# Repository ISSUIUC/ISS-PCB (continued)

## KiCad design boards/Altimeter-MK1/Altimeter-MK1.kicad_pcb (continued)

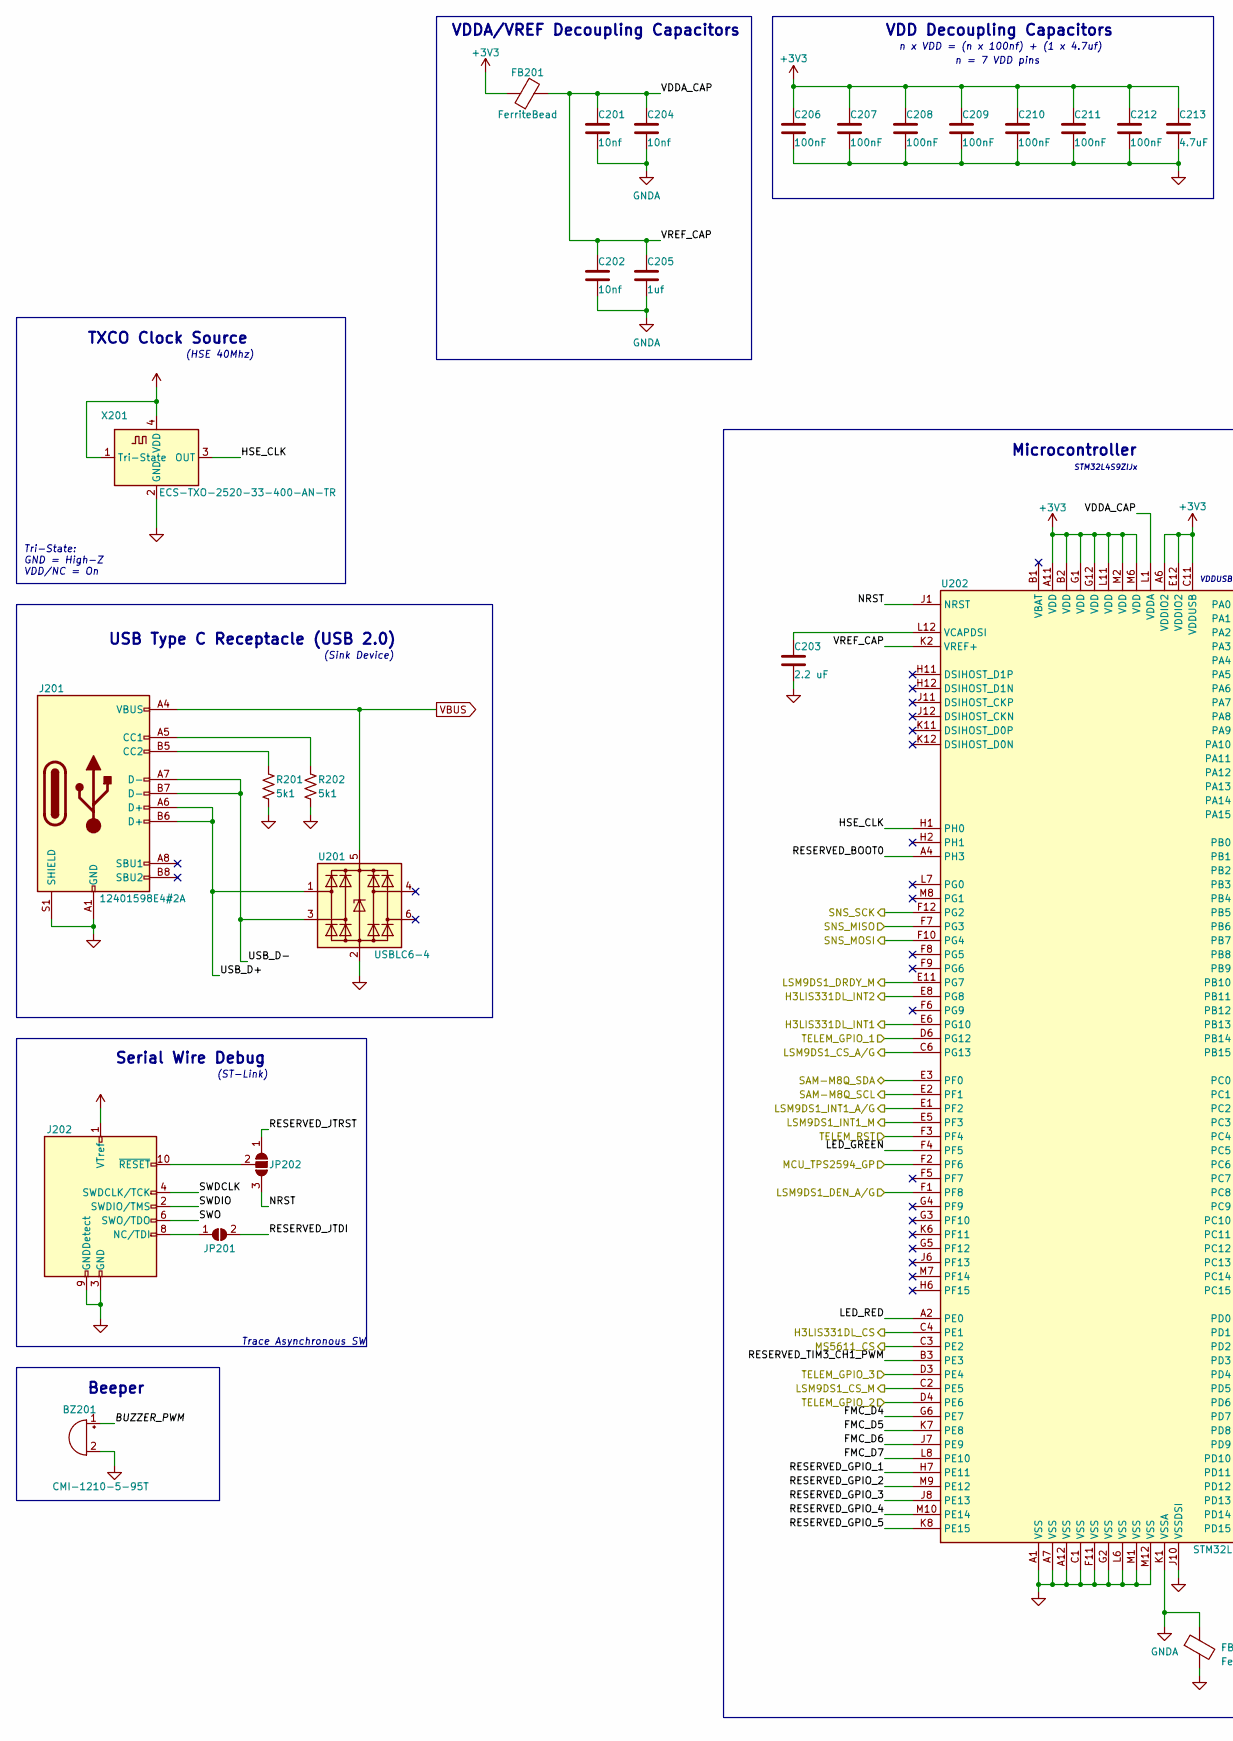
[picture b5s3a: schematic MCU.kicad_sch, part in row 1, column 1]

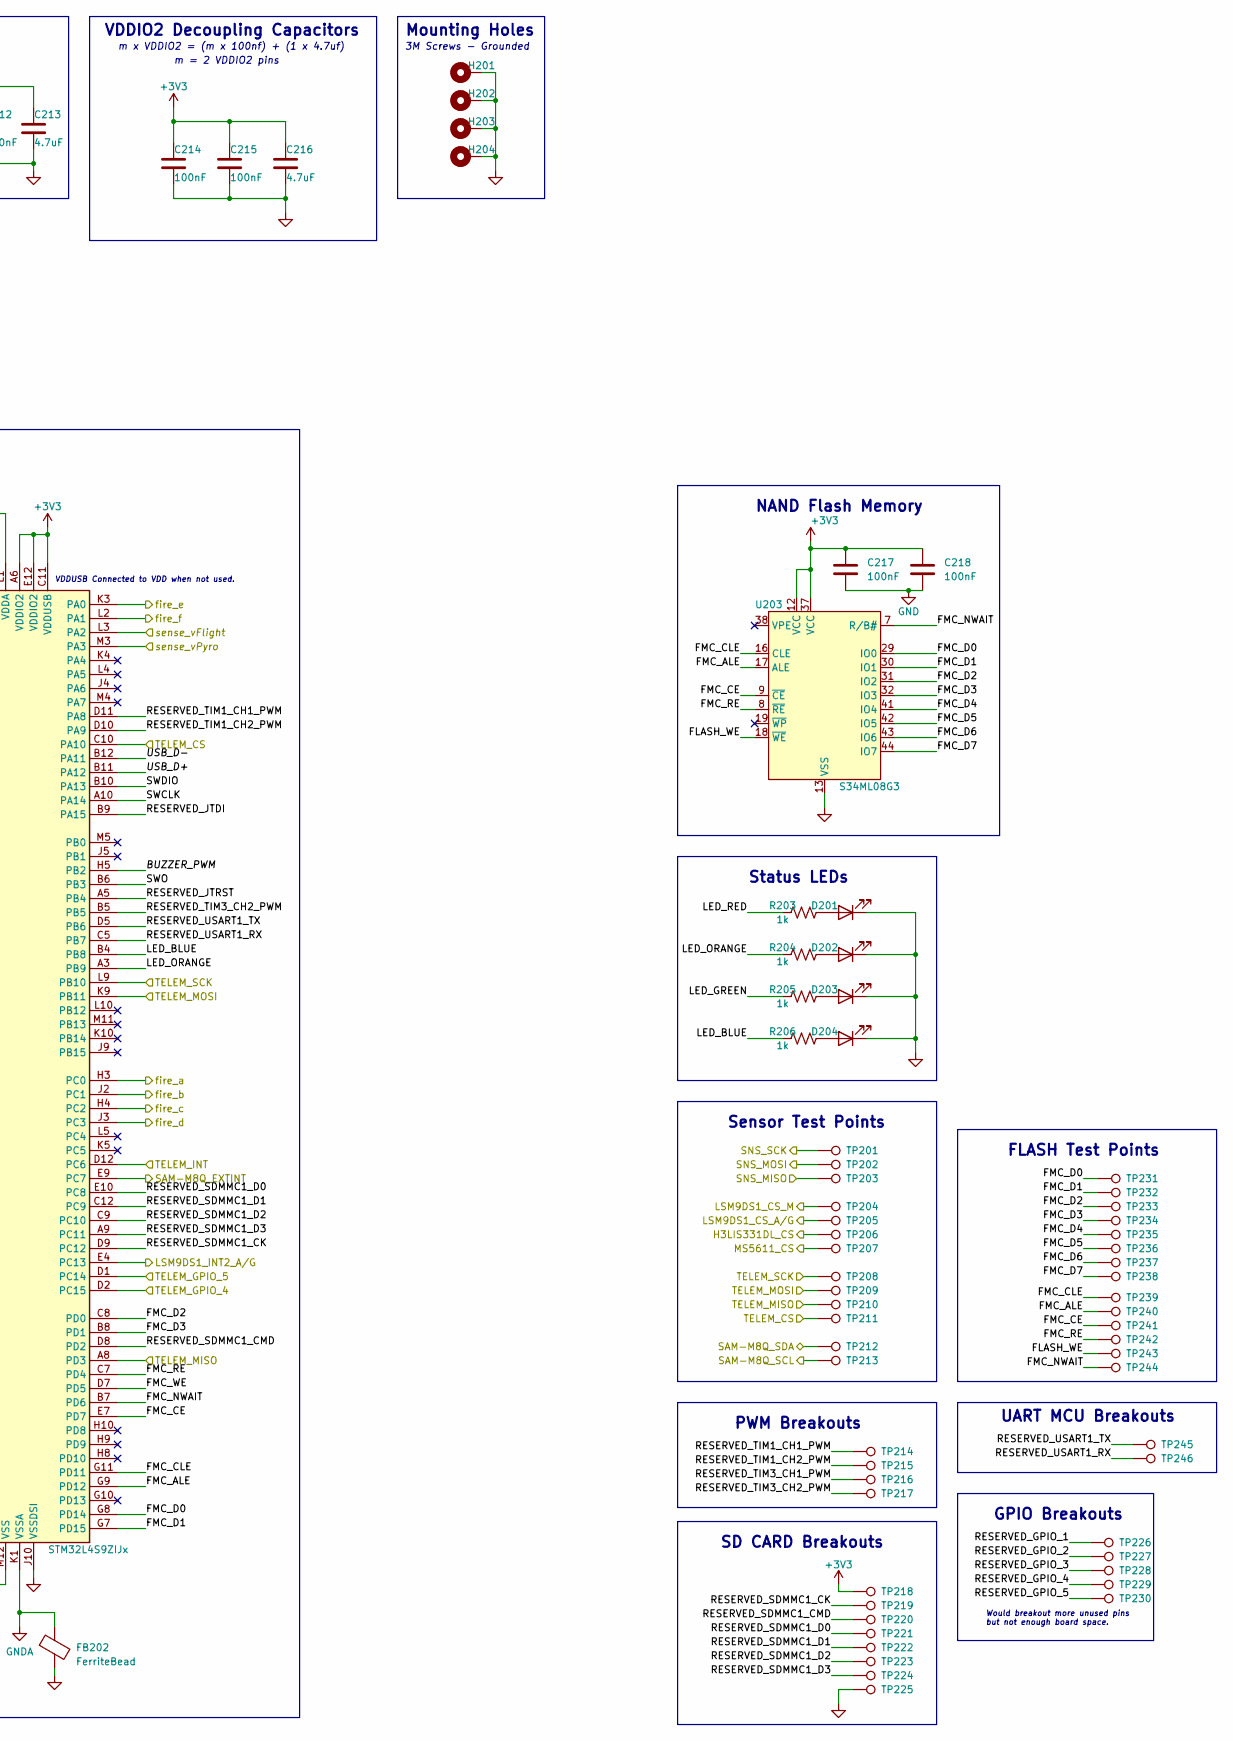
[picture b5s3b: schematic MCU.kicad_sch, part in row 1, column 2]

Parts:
BZ201: CMI-1210-5-95T; MagneticBuzzer_ProSignal_ABI-010-RC
C201, C202, C204: 10nf; C_0603_1608Metric
C203: 2.2 uF; C_0603_1608Metric
C205: 1uf; C_0603_1608Metric
C206, C207, C208, C209, C210, C211, C212, C214, C215, C217, C218: 100nF; C_0603_1608Metric
C213, C216: 4.7uF; C_0603_1608Metric
D201, D202, D203, D204: LED_0603_1608Metric
FB201, FB202: FerriteBead; R_0805_2012Metric
H201, H202, H203, H204: MountingHole_Pad; MountingHole_3.2mm_M3_Pad
J201: 12401598E4#2A; USB_C_Receptacle_Amphenol_12401548E4-2A
J202: PinHeader_1x10_P1.00mm_Vertical
JP201: SolderJumper_2_Open; SolderJumper-2_P1.3mm_Open_RoundedPad1.0x1.5mm
JP202: SolderJumper_3_Open; SolderJumper-3_P1.3mm_Open_RoundedPad1.0x1.5mm
R201, R202: 5k1; R_0603_1608Metric
R203, R204, R205, R206: 1k; R_0603_1608Metric
TP201, TP202, TP203, TP204, TP205, TP206, TP207, TP208, TP209, TP210, TP211, TP212, TP213, TP214, TP215, TP216, TP217, TP218, TP219, TP220, TP221, TP222, TP223, TP224, TP225, TP226, TP227, TP228, TP229, TP230, TP245, TP246: TestPoint; PinHeader_1x01_P1.00mm_Vertical
TP231, TP232, TP233, TP234, TP235, TP236, TP237, TP238, TP239, TP240, TP241, TP242, TP243, TP244: TestPoint; TestPoint_Pad_D1.0mm
U201: USBLC6-4; SOT-23-6
U202: STM32L4S9ZIJx; UFBGA-144_10x10mm_Layout12x12_P0.8mm
U203: S34ML08G3; TSOP-I-48_18.4x12mm_P0.5mm
X201: ECS-TXO-2520-33-400-AN-TR

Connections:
/EJECTION/fire_a: U202.H3 (PC0); also elsewhere on the board
/EJECTION/fire_b: U202.J2 (PC1); also elsewhere on the board
/EJECTION/fire_c: U202.H4 (PC2); also elsewhere on the board
/EJECTION/fire_d: U202.J3 (PC3); also elsewhere on the board
/EJECTION/fire_e: U202.K3 (PA0); also elsewhere on the board
/EJECTION/fire_f: U202.L2 (PA1); also elsewhere on the board
/EJECTION/sense_vPyro: U202.M3 (PA3); also elsewhere on the board
/MCU/BUZZER_PWM: BZ201.1 (-), U202.H5 (PB2)
/MCU/FLASH_WE: TP243.1, U203.18 (~WE)
/MCU/FMC_ALE: TP240.1, U202.G9 (PD12), U203.17 (ALE)
/MCU/FMC_CE: TP241.1, U202.E7 (PD7), U203.9 (~CE)
/MCU/FMC_CLE: TP239.1, U202.G11 (PD11), U203.16 (CLE)
/MCU/FMC_D0: TP231.1, U202.G8 (PD14), U203.29 (IO0)
/MCU/FMC_D1: TP232.1, U202.G7 (PD15), U203.30 (IO1)
/MCU/FMC_D2: TP233.1, U202.C8 (PD0), U203.31 (IO2)
/MCU/FMC_D3: TP234.1, U202.B8 (PD1), U203.32 (IO3)
/MCU/FMC_D4: TP235.1, U202.G6 (PE7), U203.41 (IO4)
/MCU/FMC_D5: TP236.1, U202.K7 (PE8), U203.42 (IO5)
/MCU/FMC_D6: TP237.1, U202.J7 (PE9), U203.43 (IO6)
/MCU/FMC_D7: TP238.1, U202.L8 (PE10), U203.44 (IO7)
/MCU/FMC_NWAIT: TP244.1, U202.B7 (PD6), U203.7 (R/B#)
/MCU/FMC_RE: TP242.1, U202.C7 (PD4), U203.8 (~RE)
/MCU/FMC_WE: U202.D7 (PD5)
/MCU/H3LIS331DL_CS: TP206.1, U202.C4 (PE1); also elsewhere on the board
/MCU/H3LIS331DL_INT1: U202.E6 (PG10); also elsewhere on the board
/MCU/H3LIS331DL_INT2: U202.E8 (PG8); also elsewhere on the board
/MCU/HSE_CLK: U202.H1 (PH0), X201.3 (OUT)
/MCU/LED_BLUE: R206.1, U202.B4 (PB8)
/MCU/LED_GREEN: R205.1, U202.F4 (PF5)
/MCU/LED_ORANGE: R204.1, U202.A3 (PB9)
/MCU/LED_RED: R203.1, U202.A2 (PE0)
/MCU/LSM9DS1_CS_A/G: TP205.1, U202.C6 (PG13); also elsewhere on the board
/MCU/LSM9DS1_CS_M: TP204.1, U202.C2 (PE5); also elsewhere on the board
/MCU/LSM9DS1_DEN_A/G: U202.F1 (PF8); also elsewhere on the board
/MCU/LSM9DS1_DRDY_M: U202.E11 (PG7); also elsewhere on the board
/MCU/LSM9DS1_INT1_A/G: U202.E1 (PF2); also elsewhere on the board
/MCU/LSM9DS1_INT1_M: U202.E5 (PF3); also elsewhere on the board
/MCU/LSM9DS1_INT2_A/G: U202.E4 (PC13); also elsewhere on the board
/MCU/MCU_TPS2594_GP: U202.F2 (PF6); also elsewhere on the board
/MCU/MS5611_CS: TP207.1, U202.C3 (PE2); also elsewhere on the board
/MCU/NRST: JP202.3 (B), U202.J1 (NRST)
/MCU/RESERVED_BOOT0: U202.A4 (PH3)
/MCU/RESERVED_GPIO_1: TP226.1, U202.H7 (PE11)
/MCU/RESERVED_GPIO_2: TP227.1, U202.M9 (PE12)
/MCU/RESERVED_GPIO_3: TP228.1, U202.J8 (PE13)
/MCU/RESERVED_GPIO_4: TP229.1, U202.M10 (PE14)
/MCU/RESERVED_GPIO_5: TP230.1, U202.K8 (PE15)
/MCU/RESERVED_JTDI: JP201.2 (B), U202.B9 (PA15)
/MCU/RESERVED_JTRST: JP202.1 (A), U202.A5 (PB4)
/MCU/RESERVED_SDMMC1_CK: TP219.1, U202.D9 (PC12)
/MCU/RESERVED_SDMMC1_CMD: TP220.1, U202.D8 (PD2)
/MCU/RESERVED_SDMMC1_D0: TP221.1, U202.E10 (PC8)
/MCU/RESERVED_SDMMC1_D1: TP222.1, U202.C12 (PC9)
/MCU/RESERVED_SDMMC1_D2: TP223.1, U202.C9 (PC10)
/MCU/RESERVED_SDMMC1_D3: TP224.1, U202.A9 (PC11)
/MCU/RESERVED_TIM1_CH1_PWM: TP214.1, U202.D11 (PA8)
/MCU/RESERVED_TIM1_CH2_PWM: TP215.1, U202.D10 (PA9)
/MCU/RESERVED_TIM3_CH1_PWM: TP216.1, U202.B3 (PE3)
/MCU/RESERVED_TIM3_CH2_PWM: TP217.1, U202.B5
/MCU/RESERVED_USART1_RX: TP246.1, U202.C5 (PB7)
/MCU/RESERVED_USART1_TX: TP245.1, U202.D5 (PB6)
/MCU/SAM-M8Q_EXTINT: U202.E9 (PC7); also elsewhere on the board
/MCU/SAM-M8Q_SCL: TP213.1, U202.E2 (PF1); also elsewhere on the board
/MCU/SAM-M8Q_SDA: TP212.1, U202.E3 (PF0); also elsewhere on the board
/MCU/SNS_MISO: TP203.1, U202.F7 (PG3); also elsewhere on the board
/MCU/SNS_MOSI: TP202.1, U202.F10 (PG4); also elsewhere on the board
/MCU/SNS_SCK: TP201.1, U202.F12 (PG2); also elsewhere on the board
/MCU/SWCLK: U202.A10 (PA14)
/MCU/SWDCLK: J202.4 (SWDCLK/TCK)
/MCU/SWDIO: J202.2 (SWDIO/TMS), U202.B10 (PA13)
/MCU/SWO: J202.6 (SWO/TDO), U202.B6 (PB3)
/MCU/TELEM_CS: TP211.1, U202.C10 (PA10); also elsewhere on the board
/MCU/TELEM_GPIO_1: U202.D6 (PG12); also elsewhere on the board
/MCU/TELEM_GPIO_2: U202.D4 (PE6); also elsewhere on the board
/MCU/TELEM_GPIO_3: U202.D3 (PE4); also elsewhere on the board
/MCU/TELEM_GPIO_4: U202.D2 (PC15); also elsewhere on the board
/MCU/TELEM_GPIO_5: U202.D1 (PC14); also elsewhere on the board
/MCU/TELEM_INT: U202.D12 (PC6); also elsewhere on the board
/MCU/TELEM_MISO: TP210.1, U202.A8 (PD3); also elsewhere on the board
/MCU/TELEM_MOSI: TP209.1, U202.K9 (PB11); also elsewhere on the board
/MCU/TELEM_RST: U202.F3 (PF4); also elsewhere on the board
/MCU/TELEM_SCK: TP208.1, U202.L9 (PB10); also elsewhere on the board
/MCU/USB_D+: J201.A6 (D+), J201.B6 (D+), U201.1 (I/O1), U202.B11 (PA12)
/MCU/USB_D-: J201.A7 (D-), J201.B7 (D-), U201.3 (I/O2), U202.B12 (PA11)
/MCU/VDDA_CAP: C201.1, C202.1, C204.1, C205.1, FB201.2, U202.K2 (VREF+), U202.L1 (VDDA)
/MCU/sense_vFlight: U202.L3 (PA2); also elsewhere on the board
GNDA: C201.2, C202.2, C204.2, C205.2, FB202.1, U202.K1 (VSSA)
unnamed: C203.1, U202.L12 (VCAPDSI)
unnamed: D201.2 (A), R203.2
unnamed: D202.2 (A), R204.2
unnamed: D203.2 (A), R205.2
unnamed: D204.2 (A), R206.2
unnamed: J201.A5 (CC1), R202.1
unnamed: J201.B5 (CC2), R201.1
unnamed: J202.8 (NC/TDI), JP201.1 (A)
unnamed: J202.10 (~RESET), JP202.2 (C)
VBUS: J201.A4 (VBUS), J201.A9 (VBUS), J201.B4 (VBUS), J201.B9 (VBUS), U201.5 (VBUS); also elsewhere on the board

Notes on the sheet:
Trace Asynchronous SW
NAND Flash Memory
VDD Decoupling Capacitors
Status LEDs
UART MCU Breakouts
Tri-State: GND = High-Z VDD/NC = On
Would breakout more unused pins but not enough board space.
FLASH Test Points
n x VDD = (n x 100nf) + (1 x 4.7uf)
VDDIO2 Decoupling Capacitors
(ST-Link)
STM32L4S9ZIJx
n = 7 VDD pins
3M Screws - Grounded
Mounting Holes
TXCO Clock Source
SD CARD Breakouts
(Sink Device)
Sensor Test Points
m = 2 VDDIO2 pins
GPIO Breakouts
VDDA/VREF Decoupling Capacitors
Beeper
PWM Breakouts
m x VDDIO2 = (m x 100nf) + (1 x 4.7uf)
(HSE 40Mhz)
USB Type C Receptacle (USB 2.0)
Microcontroller
VDDUSB Connected to VDD when not used.
Serial Wire Debug

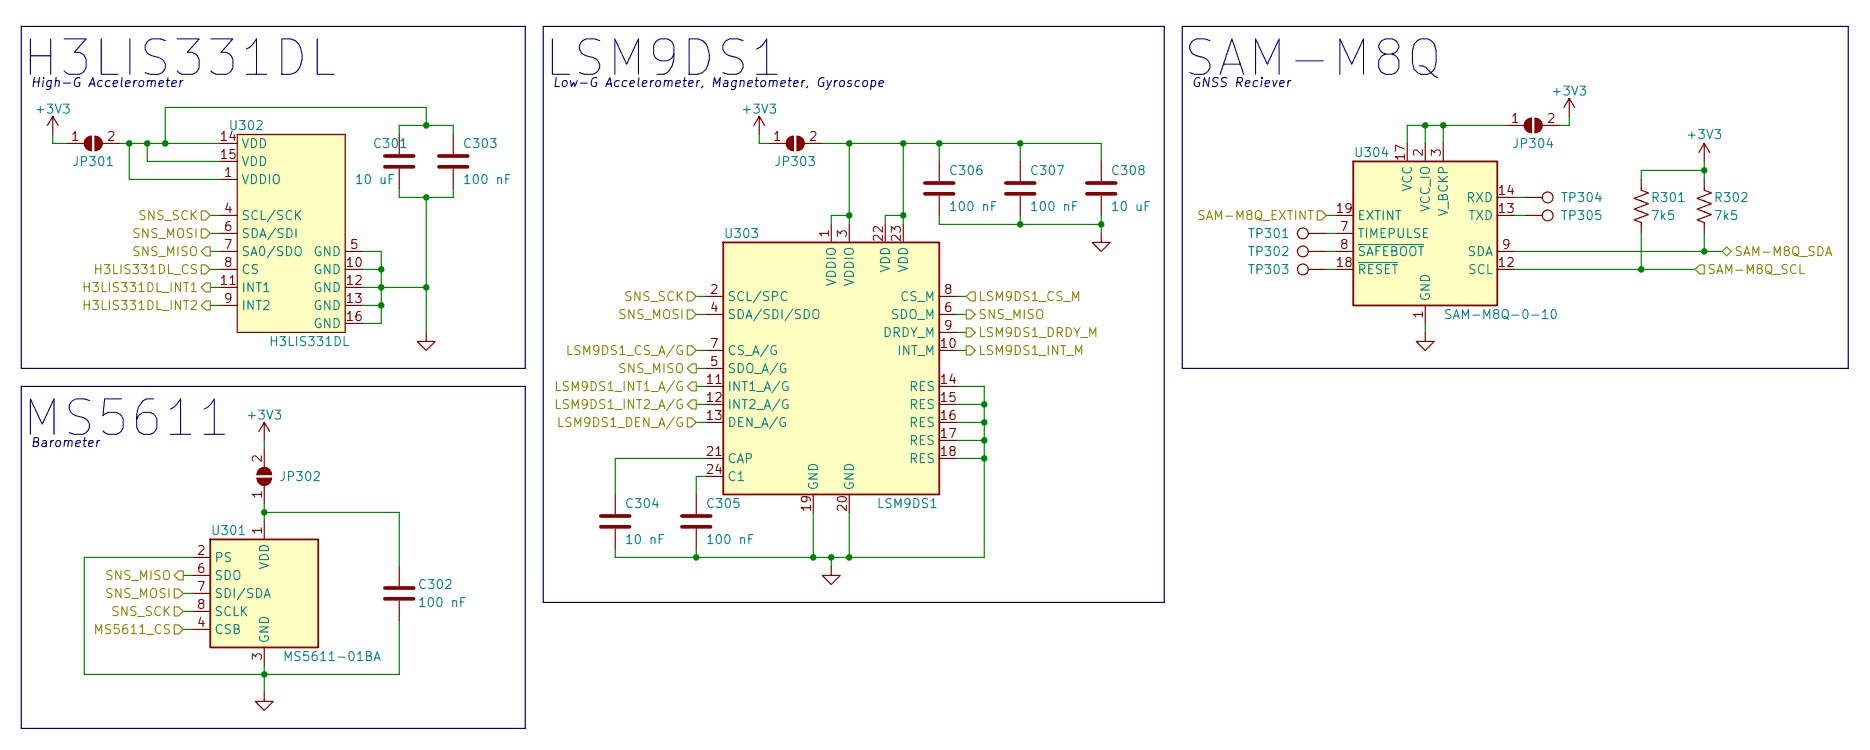
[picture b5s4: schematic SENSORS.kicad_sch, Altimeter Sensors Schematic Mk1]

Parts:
C301, C308: 10 uF; C_0603_1608Metric
C302, C303, C305, C306, C307: 100 nF; C_0603_1608Metric
C304: 10 nF; C_0603_1608Metric
JP301, JP302, JP303, JP304: SolderJumper_2_Open; SolderJumper-2_P1.3mm_Open_RoundedPad1.0x1.5mm
R301, R302: 7k5; R_0603_1608Metric
TP301, TP302, TP303, TP304, TP305: TestPoint; TestPoint_Pad_D1.0mm
U301: MS5611-01BA; LGA-8_3x5mm_P1.25mm
U302: H3LIS331DL; LGA-16_3x3mm_P0.5mm_LayoutBorder3x5y
U303: LSM9DS1; LGA-24L_3x3.5mm_P0.43mm
U304: SAM-M8Q-0-10; ublox_SAM-M8Q

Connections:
/MCU/H3LIS331DL_CS: U302.8 (CS); also elsewhere on the board
/MCU/H3LIS331DL_INT1: U302.11 (INT1); also elsewhere on the board
/MCU/H3LIS331DL_INT2: U302.9 (INT2); also elsewhere on the board
/MCU/LSM9DS1_CS_A/G: U303.7 (CS_A/G); also elsewhere on the board
/MCU/LSM9DS1_CS_M: U303.8 (CS_M); also elsewhere on the board
/MCU/LSM9DS1_DEN_A/G: U303.13 (DEN_A/G); also elsewhere on the board
/MCU/LSM9DS1_DRDY_M: U303.9 (DRDY_M); also elsewhere on the board
/MCU/LSM9DS1_INT1_A/G: U303.11 (INT1_A/G); also elsewhere on the board
/MCU/LSM9DS1_INT1_M: U303.10 (INT_M); also elsewhere on the board
/MCU/LSM9DS1_INT2_A/G: U303.12 (INT2_A/G); also elsewhere on the board
/MCU/MS5611_CS: U301.4 (CSB), U301.5 (CSB); also elsewhere on the board
/MCU/SAM-M8Q_EXTINT: U304.19 (EXTINT); also elsewhere on the board
/MCU/SAM-M8Q_SCL: R301.2, U304.12 (SCL); also elsewhere on the board
/MCU/SAM-M8Q_SDA: R302.2, U304.9 (SDA); also elsewhere on the board
/MCU/SNS_MISO: U301.6 (SDO), U302.7 (SA0/SDO), U303.5 (SDO_A/G), U303.6 (SDO_M); also elsewhere on the board
/MCU/SNS_MOSI: U301.7 (SDI/SDA), U302.6 (SDA/SDI), U303.4 (SDA/SDI/SDO); also elsewhere on the board
/MCU/SNS_SCK: U301.8 (SCLK), U302.4 (SCL/SCK), U303.2 (SCL/SPC); also elsewhere on the board
unnamed: C301.1, C303.1, JP301.2 (B), U302.1 (VDDIO), U302.14 (VDD), U302.15 (VDD)
unnamed: C302.1, JP302.1 (A), U301.1 (VDD)
unnamed: C304.1, U303.21 (CAP)
unnamed: C305.1, U303.24 (C1)
unnamed: C306.1, C307.1, C308.1, JP303.2 (B), U303.1 (VDDIO), U303.3 (VDDIO), U303.22 (VDD), U303.23 (VDD)
unnamed: JP304.1 (A), U304.2 (VCC_IO), U304.3 (V_BCKP), U304.17 (VCC)
unnamed: TP301.1, U304.7 (TIMEPULSE)
unnamed: TP302.1, U304.8 (~SAFEBOOT)
unnamed: TP303.1, U304.18 (~RESET)
unnamed: TP304.1, U304.14 (RXD)
unnamed: TP305.1, U304.13 (TXD)

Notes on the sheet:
SAM-M8Q
High-G Accelerometer
MS5611
Barometer
LSM9DS1
GNSS Reciever
H3LIS331DL
Low-G Accelerometer, Magnetometer, Gyroscope

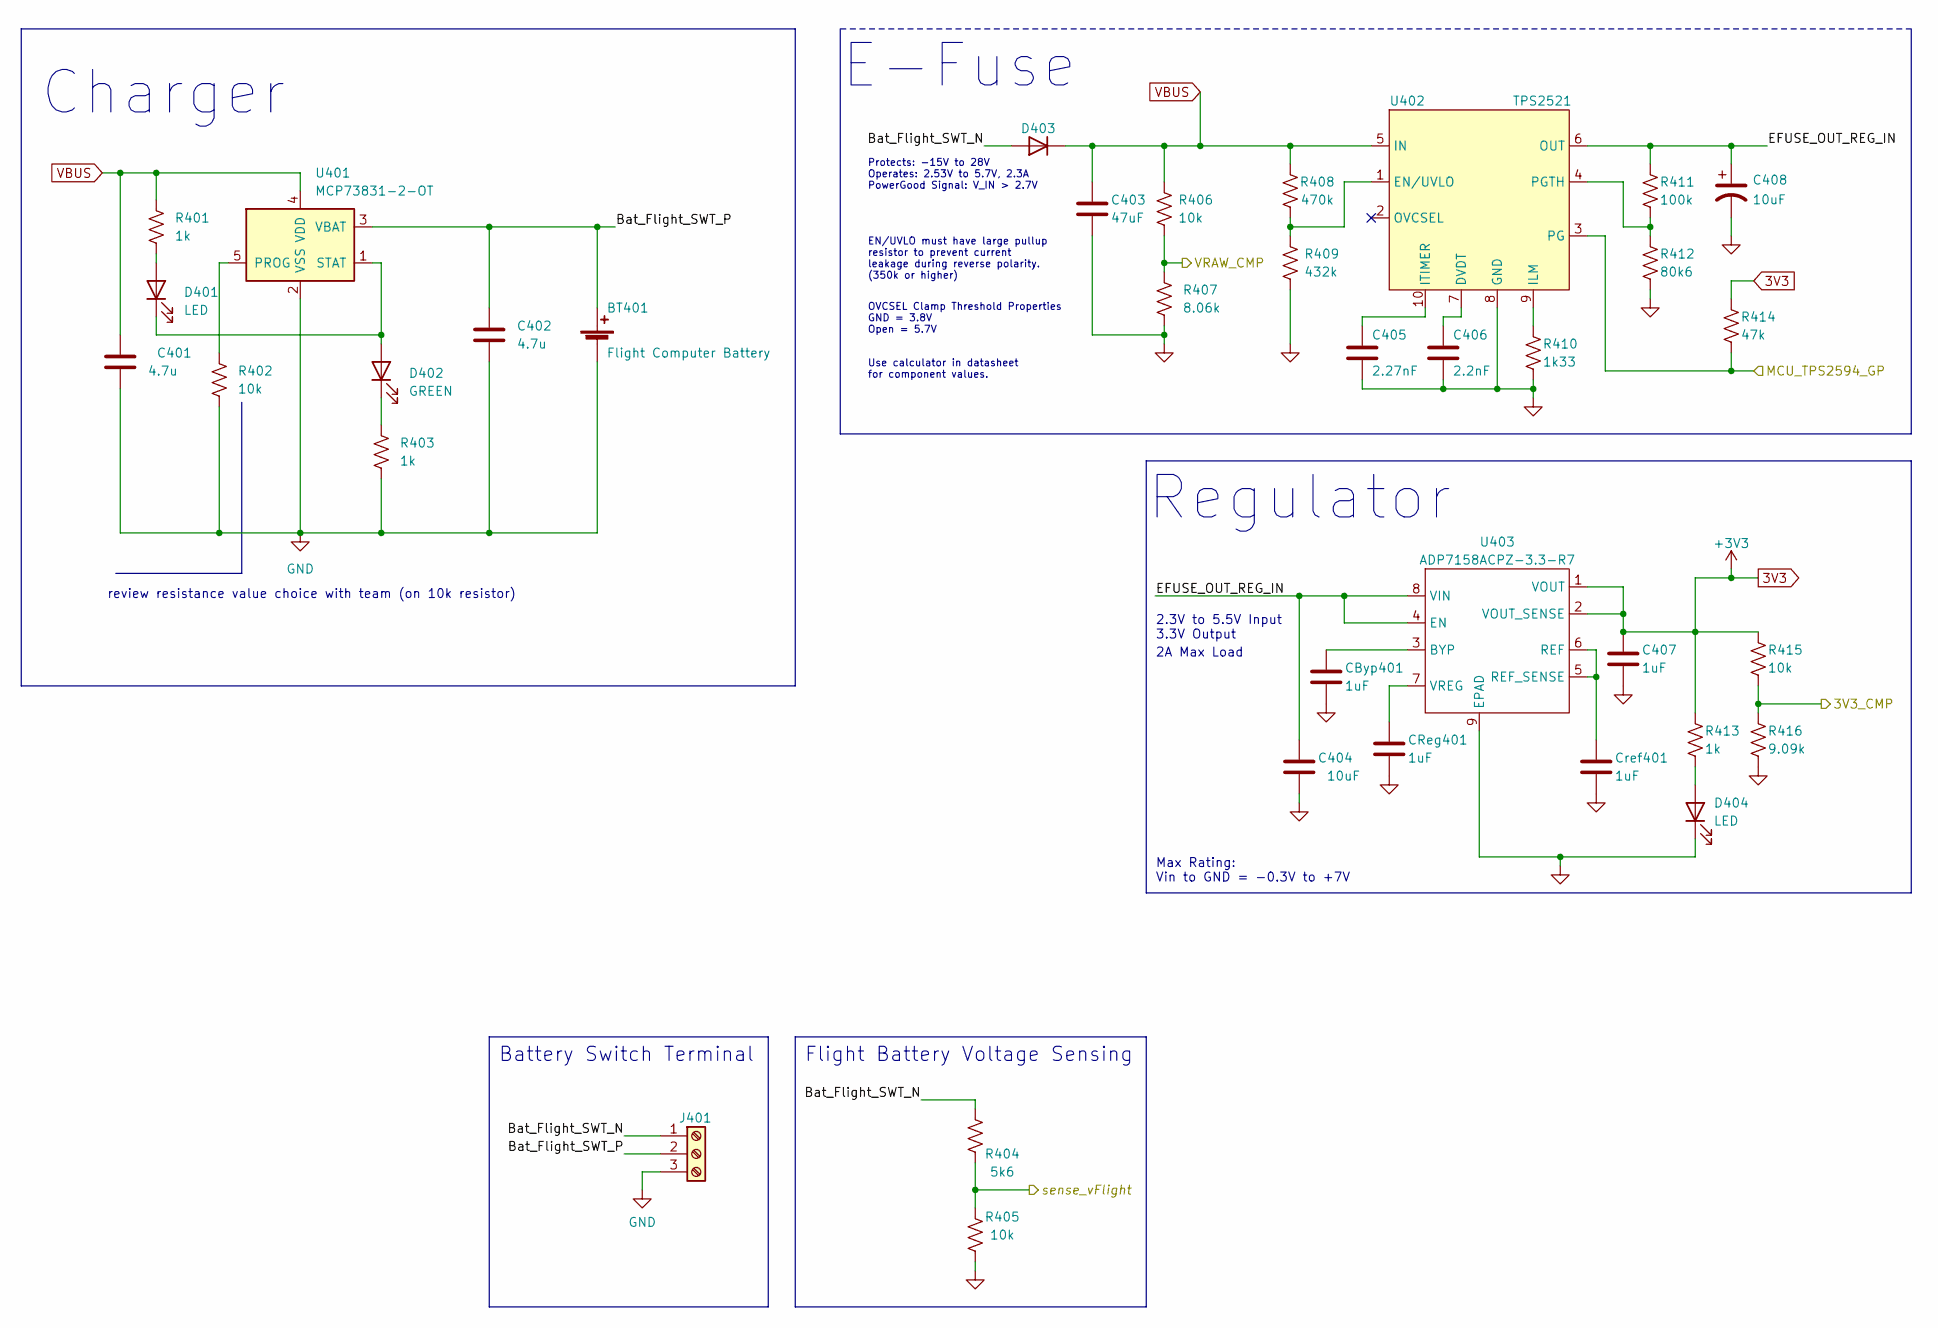
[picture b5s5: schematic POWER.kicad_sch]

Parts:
BT401: Flight Computer Battery; JST_PH_B2B-PH-K_1x02_P2.00mm_Vertical
C401, C402: 4.7u; C_0603_1608Metric
C403: 47uF; C_0603_1608Metric
C404: 10uF; C_0603_1608Metric
C405: 2.27nF; C_0603_1608Metric; Tolerance 10%
C406: 2.2nF; C_0603_1608Metric; Tolerance 10%
C407: 1uF; C_0603_1608Metric
C408: 10uF; C_0805_2012Metric; Tolerance 10%
CByp401: 1uF; C_0603_1608Metric
CReg401: 1uF; C_0603_1608Metric
Cref401: 1uF; C_0603_1608Metric
D401, D404: LED; LED_0603_1608Metric
D402: GREEN; LED_0603_1608Metric
D403: D; D_0603_1608Metric
J401: TE_1776113-3
R401, R403, R413: 1k; R_0603_1608Metric
R402, R405, R406, R415: 10k; R_0603_1608Metric
R404: 5k6; R_0603_1608Metric
R407: 8.06k; R_0603_1608Metric
R408: 470k; R_0603_1608Metric; Tolerance 1%
R409: 432k; R_0603_1608Metric; Tolerance 1%
R410: 1k33; R_0603_1608Metric; Tolerance 1%
R411: 100k; R_0603_1608Metric; Tolerance 1%
R412: 80k6; R_0603_1608Metric; Tolerance 1%
R414: 47k; R_0603_1608Metric
R416: 9.09k; R_0603_1608Metric
U401: MCP73831-2-OT; SOT-23-5
U402: TPS2521; TPS25210LRPWR
U403: ADP7158ACPZ-3.3-R7

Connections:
/EJECTION/3V3_CMP: R415.2, R416.1; also elsewhere on the board
/EJECTION/VRAW_CMP: R406.2, R407.1; also elsewhere on the board
/MCU/MCU_TPS2594_GP: R414.2, U402.3 (PG); also elsewhere on the board
/MCU/sense_vFlight: R404.1, R405.1; also elsewhere on the board
/POWER/Bat_Flight_SWT_N: D403.2 (A), J401.1, R404.2
/POWER/Bat_Flight_SWT_P: BT401.1 (+), C402.1, J401.2, U401.3 (VBAT)
/POWER/EFUSE_OUT_REG_IN: C404.1, C408.1, R411.1, U402.6 (OUT), U403.4 (EN), U403.8 (VIN)
unnamed: C405.1, U402.10 (ITIMER)
unnamed: C406.1, U402.7 (DVDT)
unnamed: CByp401.1, U403.3 (BYP)
unnamed: CReg401.1, U403.7 (VREG)
unnamed: Cref401.1, U403.5 (REF_SENSE), U403.6 (REF)
unnamed: D401.1 (K), D402.2 (A), U401.1 (STAT)
unnamed: D401.2 (A), R401.2
unnamed: D402.1 (K), R403.1
unnamed: D404.2 (A), R413.2
unnamed: R402.1, U401.5 (PROG)
unnamed: R408.1, R409.1, U402.1 (EN/UVLO)
unnamed: R410.1, U402.9 (ILM)
unnamed: R411.2, R412.1, U402.4 (PGTH)
VBUS: C401.1, C403.1, D403.1 (K), R401.1, R406.1, R408.2, U401.4 (VDD), U402.5 (IN); also elsewhere on the board

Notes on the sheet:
OVCSEL Clamp Threshold Properties GND = 3.8V Open = 5.7V
review resistance value choice with team (on 10k resistor)
Max Rating: Vin to GND = -0.3V to +7V
Charger
Flight Battery Voltage Sensing
EN/UVLO must have large pullup resistor to prevent current leakage during reverse polarity. (350k or higher)
Use calculator in datasheet for component values.
Regulator
Battery Switch Terminal
E-Fuse
2.3V to 5.5V Input 3.3V Output
Protects: -15V to 28V Operates: 2.53V to 5.7V, 2.3A PowerGood Signal: V_IN > 2.7V
2A Max Load

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
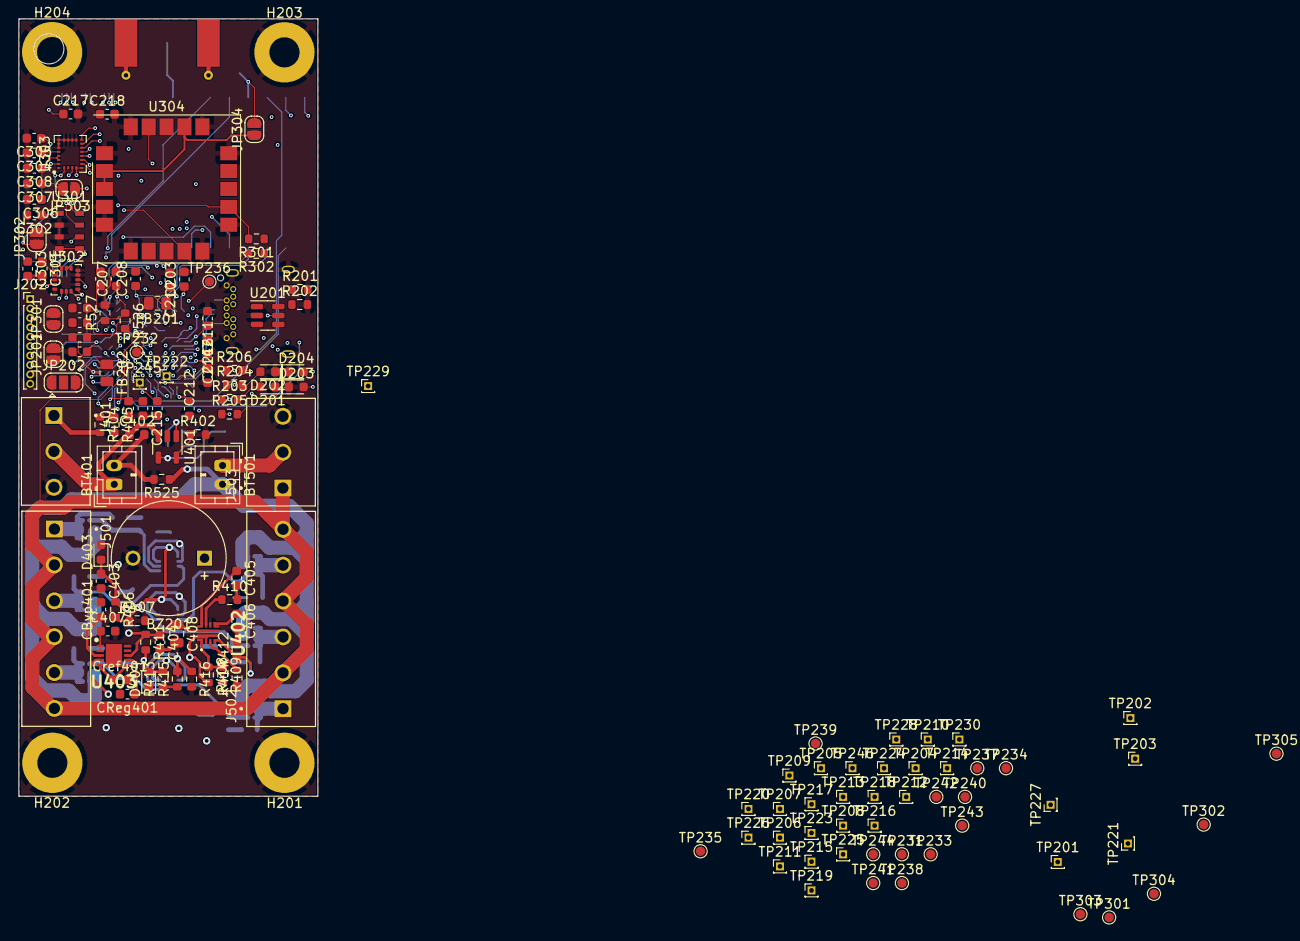
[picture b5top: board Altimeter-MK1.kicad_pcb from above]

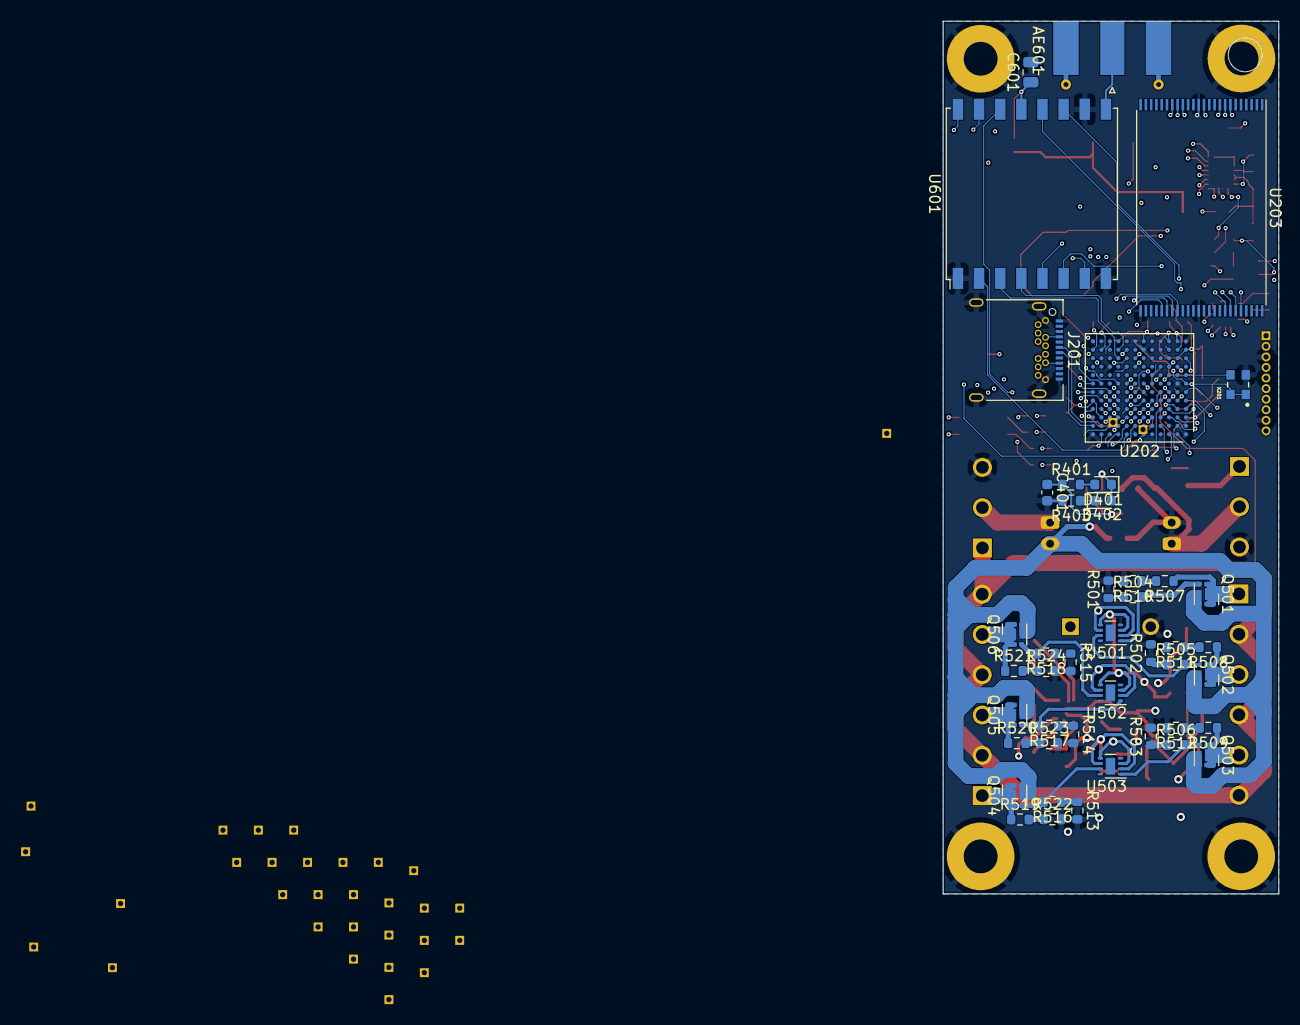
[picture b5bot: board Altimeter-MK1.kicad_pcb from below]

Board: 6 copper layers, 31.8 x 82.6 mm, 191 parts (45 on the bottom side), 146 nets.
